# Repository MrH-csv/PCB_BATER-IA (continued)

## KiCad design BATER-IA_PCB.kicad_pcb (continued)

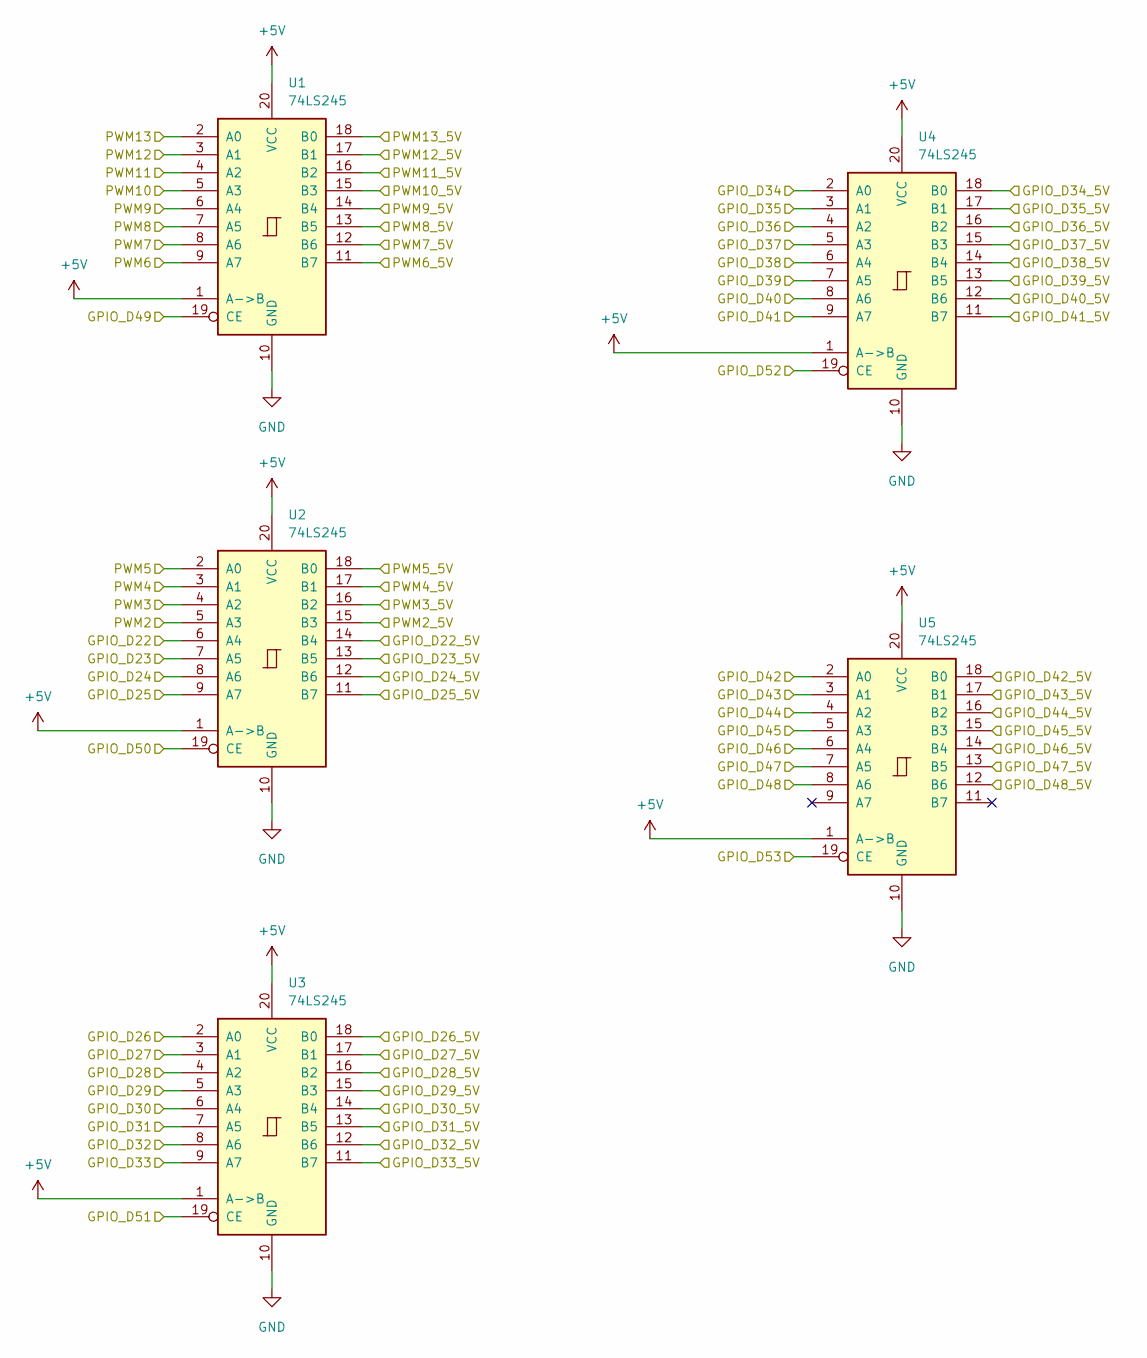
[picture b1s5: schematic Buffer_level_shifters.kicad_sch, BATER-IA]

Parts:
U1, U2, U3, U4, U5: 74LS245; DIP-20_W7.62mm_LongPads

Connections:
+5V: U1.1 (A->B), U1.20 (VCC), U2.1 (A->B), U2.20 (VCC), U3.1 (A->B), U3.20 (VCC), U4.1 (A->B), U4.20 (VCC), U5.1 (A->B), U5.20 (VCC); also elsewhere on the board
/BUFFER LEVEL SHIFTER/GPIO_D43_5V: U5.17 (B1); also elsewhere on the board
/BUFFER LEVEL SHIFTER/GPIO_D44_5V: U5.16 (B2); also elsewhere on the board
/BUFFER LEVEL SHIFTER/GPIO_D45_5V: U5.15 (B3); also elsewhere on the board
/BUFFER LEVEL SHIFTER/GPIO_D46_5V: U5.14 (B4); also elsewhere on the board
/BUFFER LEVEL SHIFTER/GPIO_D47_5V: U5.13 (B5); also elsewhere on the board
/BUFFER LEVEL SHIFTER/GPIO_D48_5V: U5.12 (B6); also elsewhere on the board
/BUFFER LEVEL SHIFTER/PWM2_5V: U2.15 (B3); also elsewhere on the board
/BUFFER LEVEL SHIFTER/PWM3_5V: U2.16 (B2); also elsewhere on the board
/BUFFER LEVEL SHIFTER/PWM4_5V: U2.17 (B1); also elsewhere on the board
D22: U2.6 (A4); also elsewhere on the board
D22_5V: U2.14 (B4); also elsewhere on the board
D23: U2.7 (A5); also elsewhere on the board
D23_5V: U2.13 (B5); also elsewhere on the board
D24: U2.8 (A6); also elsewhere on the board
D24_5V: U2.12 (B6); also elsewhere on the board
D25: U2.9 (A7); also elsewhere on the board
D25_5V: U2.11 (B7); also elsewhere on the board
D26: U3.2 (A0); also elsewhere on the board
D26_5V: U3.18 (B0); also elsewhere on the board
D27: U3.3 (A1); also elsewhere on the board
D27_5V: U3.17 (B1); also elsewhere on the board
D28: U3.4 (A2); also elsewhere on the board
D28_5V: U3.16 (B2); also elsewhere on the board
D29: U3.5 (A3); also elsewhere on the board
D29_5V: U3.15 (B3); also elsewhere on the board
D30: U3.6 (A4); also elsewhere on the board
D30_5V: U3.14 (B4); also elsewhere on the board
D31: U3.7 (A5); also elsewhere on the board
D31_5V: U3.13 (B5); also elsewhere on the board
D32: U3.8 (A6); also elsewhere on the board
D32_5V: U3.12 (B6); also elsewhere on the board
D33: U3.9 (A7); also elsewhere on the board
D33_5V: U3.11 (B7); also elsewhere on the board
D34: U4.2 (A0); also elsewhere on the board
D34_5V: U4.18 (B0); also elsewhere on the board
D35: U4.3 (A1); also elsewhere on the board
D35_5V: U4.17 (B1); also elsewhere on the board
D36: U4.4 (A2); also elsewhere on the board
D36_5V: U4.16 (B2); also elsewhere on the board
D37: U4.5 (A3); also elsewhere on the board
D37_5V: U4.15 (B3); also elsewhere on the board
D38: U4.6 (A4); also elsewhere on the board
D38_5V: U4.14 (B4); also elsewhere on the board
D39: U4.7 (A5); also elsewhere on the board
D39_5V: U4.13 (B5); also elsewhere on the board
D40: U4.8 (A6); also elsewhere on the board
D40_5V: U4.12 (B6); also elsewhere on the board
D41: U4.9 (A7); also elsewhere on the board
D41_5V: U4.11 (B7); also elsewhere on the board
D42: U5.2 (A0); also elsewhere on the board
D42_5V: U5.18 (B0); also elsewhere on the board
D43: U5.3 (A1); also elsewhere on the board
D44: U5.4 (A2); also elsewhere on the board
D45: U5.5 (A3); also elsewhere on the board
D46: U5.6 (A4); also elsewhere on the board
D47: U5.7 (A5); also elsewhere on the board
D48: U5.8 (A6); also elsewhere on the board
D49: U1.19 (CE); also elsewhere on the board
D50: U2.19 (CE); also elsewhere on the board
D51: U3.19 (CE); also elsewhere on the board
D52: U4.19 (CE); also elsewhere on the board
D53: U5.19 (CE); also elsewhere on the board
GND: U1.10 (GND), U2.10 (GND), U3.10 (GND), U4.10 (GND), U5.10 (GND); also elsewhere on the board
PWM_02: U2.5 (A3); also elsewhere on the board
PWM_03: U2.4 (A2); also elsewhere on the board
PWM_04: U2.3 (A1); also elsewhere on the board
PWM_05: U2.2 (A0); also elsewhere on the board
PWM_5V_GP_1: U1.16 (B2); also elsewhere on the board
PWM_5V_GP_2: U1.17 (B1); also elsewhere on the board
PWM_5V_GP_3: U1.18 (B0); also elsewhere on the board
PWM_06: U1.9 (A7); also elsewhere on the board
PWM_07: U1.8 (A6); also elsewhere on the board
PWM_08: U1.7 (A5); also elsewhere on the board
PWM_09: U1.6 (A4); also elsewhere on the board
PWM_10: U1.5 (A3); also elsewhere on the board
PWM_11: U1.4 (A2); also elsewhere on the board
PWM_12: U1.3 (A1); also elsewhere on the board
PWM_13: U1.2 (A0); also elsewhere on the board
PWM_SERVO_1: U2.18 (B0); also elsewhere on the board
PWM_SERVO_2: U1.11 (B7); also elsewhere on the board
PWM_SERVO_3: U1.12 (B6); also elsewhere on the board
PWM_SERVO_4: U1.13 (B5); also elsewhere on the board
PWM_SERVO_5: U1.14 (B4); also elsewhere on the board
PWM_SERVO_6: U1.15 (B3); also elsewhere on the board

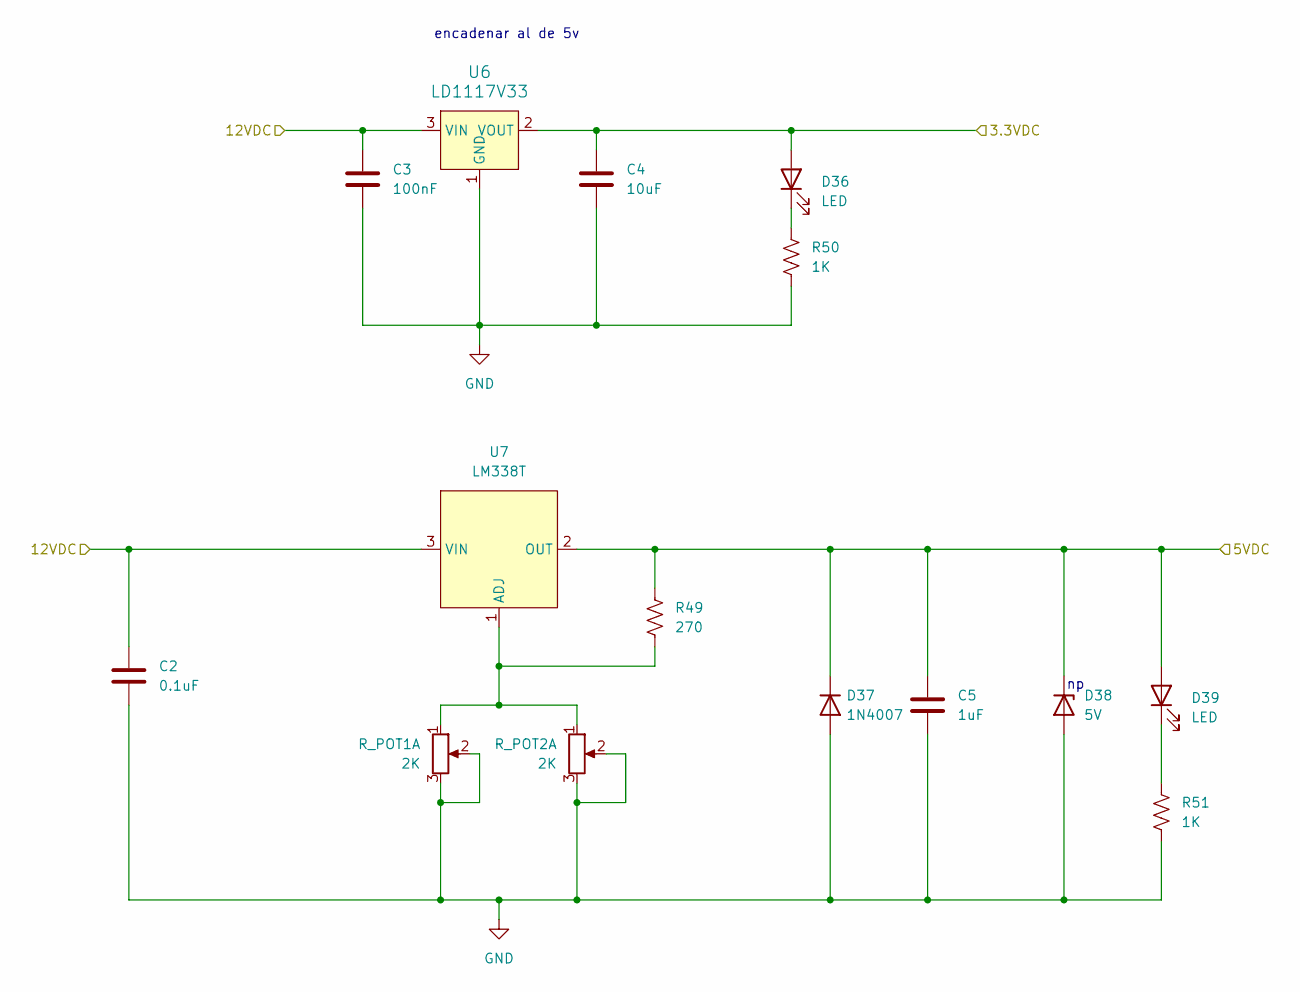
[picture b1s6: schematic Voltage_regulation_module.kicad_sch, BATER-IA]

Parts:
C2: 0.1uF; C_Radial_D10.0mm_H12.5mm_P5.00mm
C3: 100nF; C_Disc_D8.0mm_W5.0mm_P5.00mm
C4: 10uF; CP_Radial_D8.0mm_P5.00mm
C5: 1uF; C_Radial_D10.0mm_H12.5mm_P5.00mm
D36, D39: LED; LED_D3.0mm
D37: 1N4007; D_DO-41_SOD81_P10.16mm_Horizontal
D38: 5V; D_DO-35_SOD27_P10.16mm_Horizontal
R49: 270; R_Axial_DIN0411_L9.9mm_D3.6mm_P12.70mm_Horizontal
R50, R51: 1K; R_Axial_DIN0204_L3.6mm_D1.6mm_P5.08mm_Horizontal
R_POT1, R_POT2: 2K; Potentiometer_Bourns_3296W_Vertical
U6: LD1117V33; TO-220-3_Vertical; MPN LD1117V33; Digi-Key_PN 497-1491-5-ND
U7: LM338T; TO-220-3_Vertical

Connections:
+3.3V: C4.1, D36.2 (A), U6.2 (VOUT); also elsewhere on the board
+5V: C5.1, D37.1 (K), D38.1 (K), D39.2 (A), R49.1, U7.2 (OUT); also elsewhere on the board
+12V: C2.1, C3.1, U6.3 (VIN), U7.3 (VIN); also elsewhere on the board
GND: C2.2, C3.2, C4.2, C5.2, D37.2 (A), D38.2 (A), R50.2, R51.2, R_POT1.2, R_POT1.3, R_POT2.2, R_POT2.3, U6.1 (GND); also elsewhere on the board
unnamed: D36.1 (K), R50.1
unnamed: D39.1 (K), R51.1
unnamed: R49.2, R_POT1.1, R_POT2.1, U7.1 (ADJ)

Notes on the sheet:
encadenar al de 5v

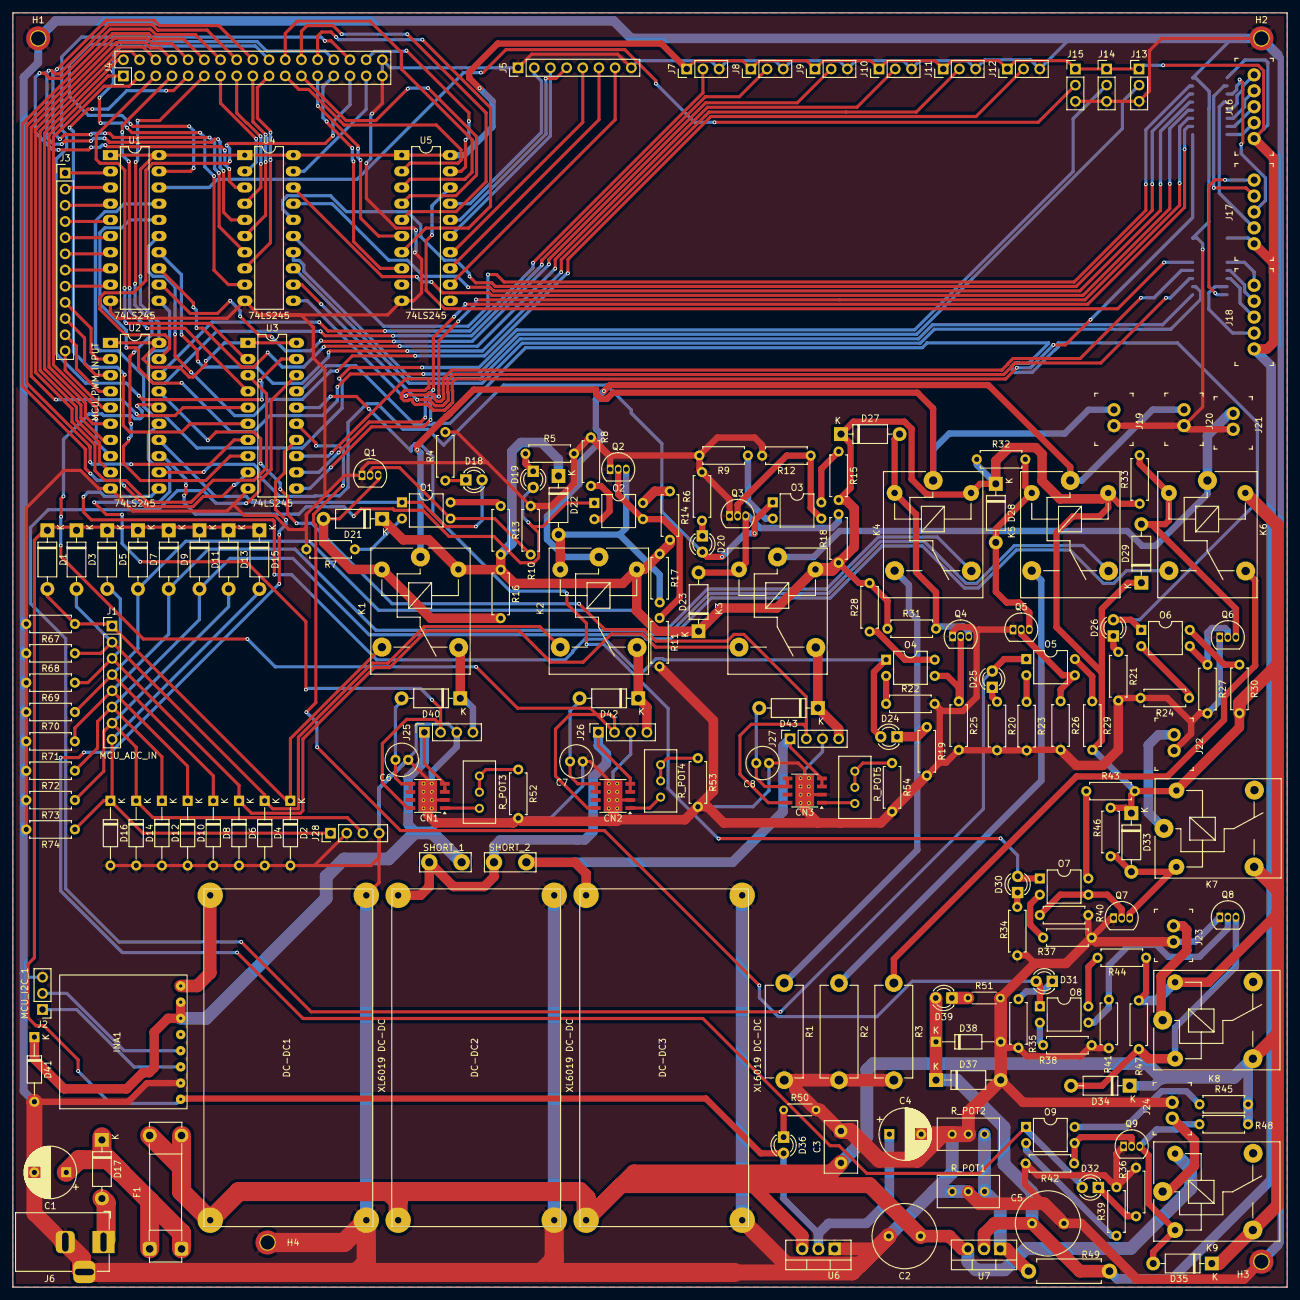
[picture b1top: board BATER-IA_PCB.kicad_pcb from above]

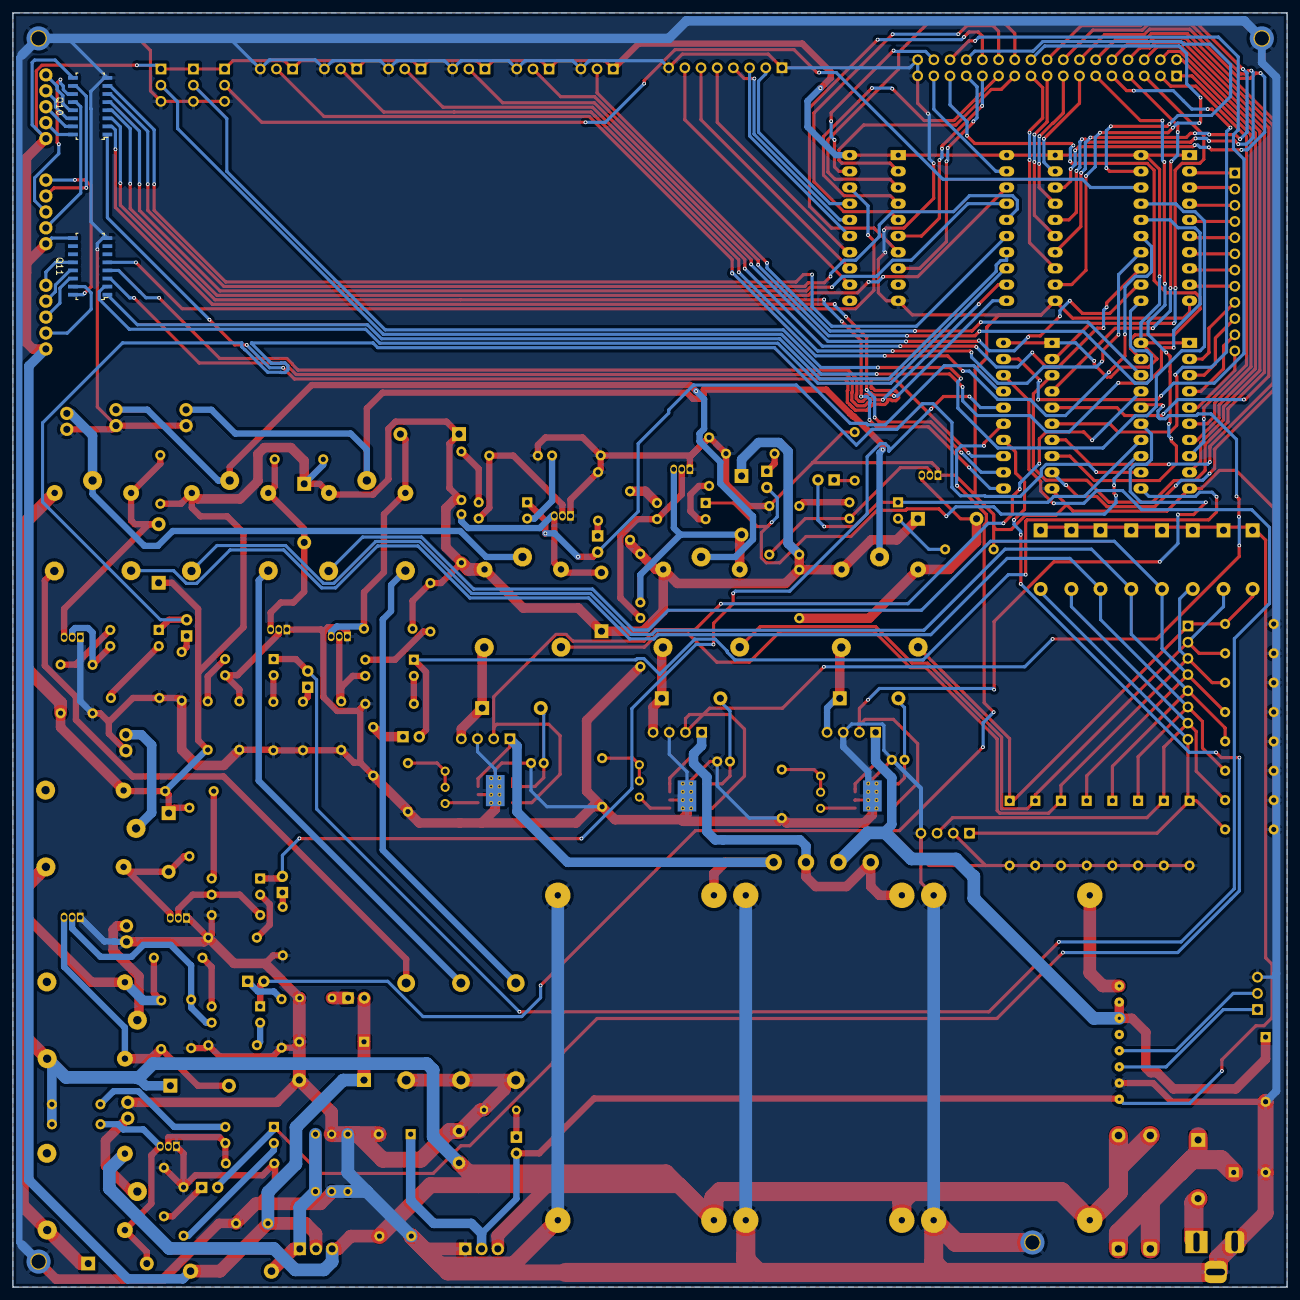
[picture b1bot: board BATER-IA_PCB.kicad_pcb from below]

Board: 2 copper layers, 200.0 x 200.0 mm, 196 parts (2 on the bottom side), 184 nets.

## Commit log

2024-11-05 PCB initial state
    The DC power stage routes were routed. Also the dimentions of the UDOO board was used to place the pin headers.
2024-11-07 BUGFIX: The Diagram error in to relay module was fixed.
    The routing error in the relay diagram was fixed, also, a prototype of the relay circuit was build and the functionality was validated satisfactorily
2024-11-07 Diagram updated... (in process only to backup).
2024-11-09 PCB REV 001 design
    The design of the first revition of the PCB is complete.
2024-11-10 PCB 90% & Corrections to diagram in the ADC section were done
    Te resistors to secure a low logical level were placed, also the routing of the PCB is at the 90%
2024-11-11 Rev 01 has been finished
    gerber files , drill files and map drill has been generated
2024-11-14 Backup
2024-11-26 Diagram updated with the pending bugfix
